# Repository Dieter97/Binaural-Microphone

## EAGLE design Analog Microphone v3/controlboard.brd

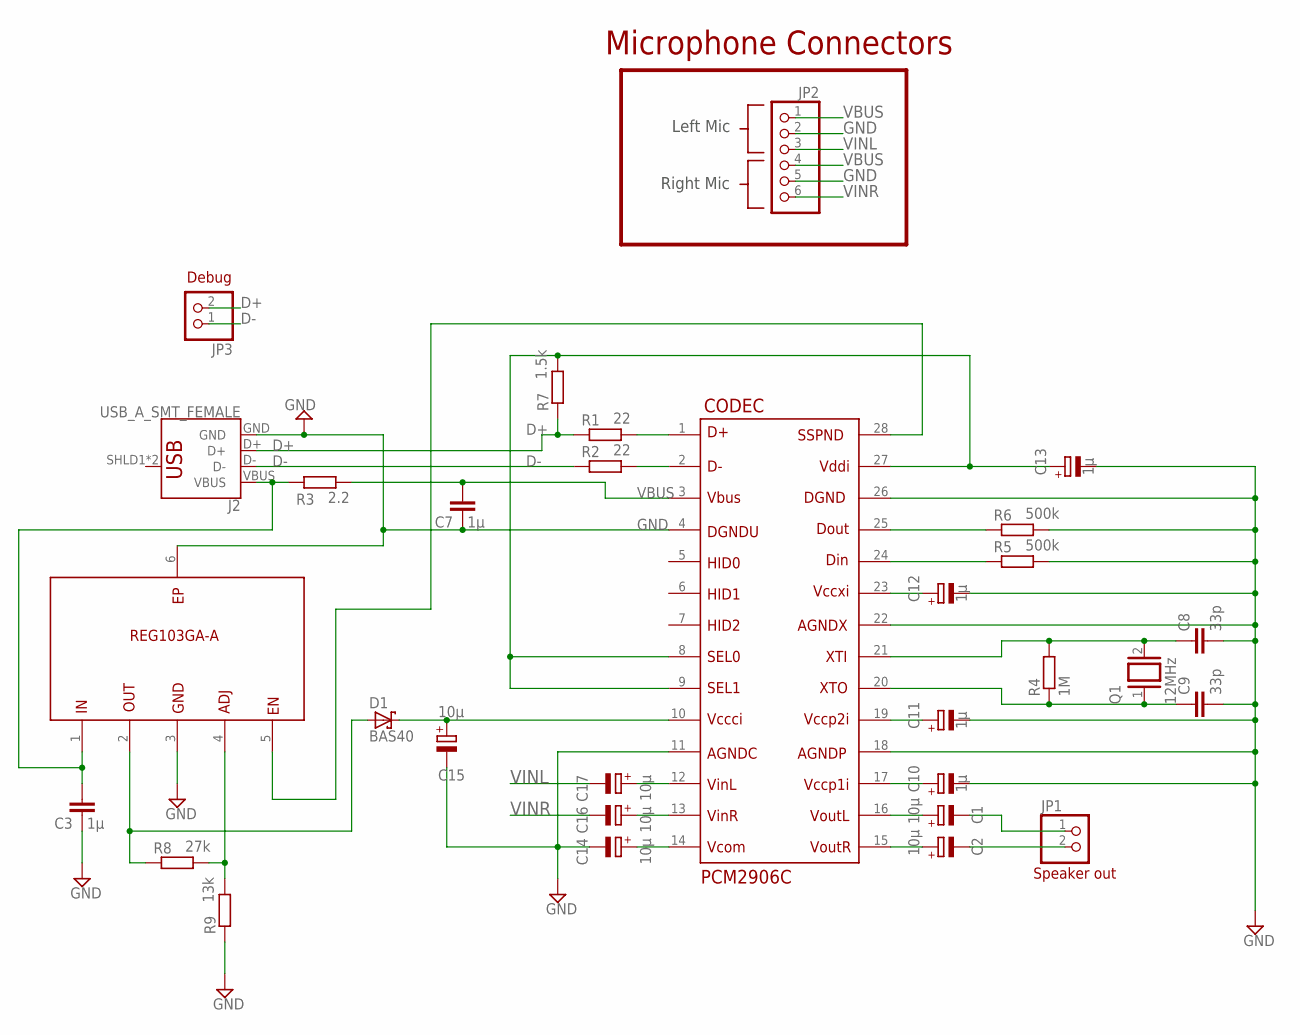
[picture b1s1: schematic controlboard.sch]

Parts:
C1, C2, C14, C15, C16, C17: 10µ; 153CLV-0807
C3, C7: 1µ; C0805
C8, C9: 33p; C0805
C10, C11, C12, C13: 1µ; 153CLV-0807
CODEC: PCM2906C; SOP65P780X200-28N
D1: BAS40; SOT23
J2: USB_A_SMT_FEMALE; USB-A-S-SILK-FEMALE
JP1, JP3: PINHD-1X2; 1X02
JP2: PINHD-1X6; 1X06
Q1: 12MHz; QS
R1, R2: 22; R0805
R3: 2.2; R0805
R4: 1M; R0805
R5, R6: 500k; R0805
R7: 1.5k; R0805
R8: 27k; R0805
R9: 13k; R0805
U$1: REG103GA-A; SOT127P706X180-6N

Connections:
D+: J2.D+, JP3.2, R1.1, R7.1
D-: J2.D-, JP3.1, R2.1
GND: C3.1, C7.1, C8.2, C9.2, C10.-, C11.-, C12.-, C13.-, C14.-, C15.-, CODEC.4, CODEC.11, CODEC.18, CODEC.22, CODEC.26, J2.GND, JP2.2, JP2.5, R5.2, R6.2, R9.1, U$1.3, U$1.6
unnamed: CODEC.1, R1.2
unnamed: CODEC.2, R2.2
unnamed: C11.+, CODEC.19
unnamed: C9.1, CODEC.20, Q1.1, R4.1
unnamed: C8.1, CODEC.21, Q1.2, R4.2
unnamed: C10.+, CODEC.17
unnamed: C12.+, CODEC.23
unnamed: CODEC.25, R6.1
unnamed: CODEC.24, R5.1
unnamed: C13.+, CODEC.8, CODEC.9, CODEC.27, R7.2
unnamed: C15.+, CODEC.10, D1.3 (C)
unnamed: C14.+, CODEC.14
unnamed: CODEC.28, U$1.5
unnamed: C1.+, CODEC.16
unnamed: C2.+, CODEC.15
unnamed: C17.+, CODEC.12
unnamed: C16.+, CODEC.13
unnamed: C1.-, JP1.1
unnamed: C2.-, JP1.2
unnamed: R8.2, R9.2, U$1.4
unnamed: D1.1 (A), R8.1, U$1.2
unnamed: C3.2, J2.VBUS, R3.1, U$1.1
VBUS: C7.2, CODEC.3, JP2.1, JP2.4, R3.2
VINL: C17.-, JP2.3
VINR: C16.-, JP2.6

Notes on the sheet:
Left Mic
Right Mic
Microphone Connectors
Speaker out
Debug

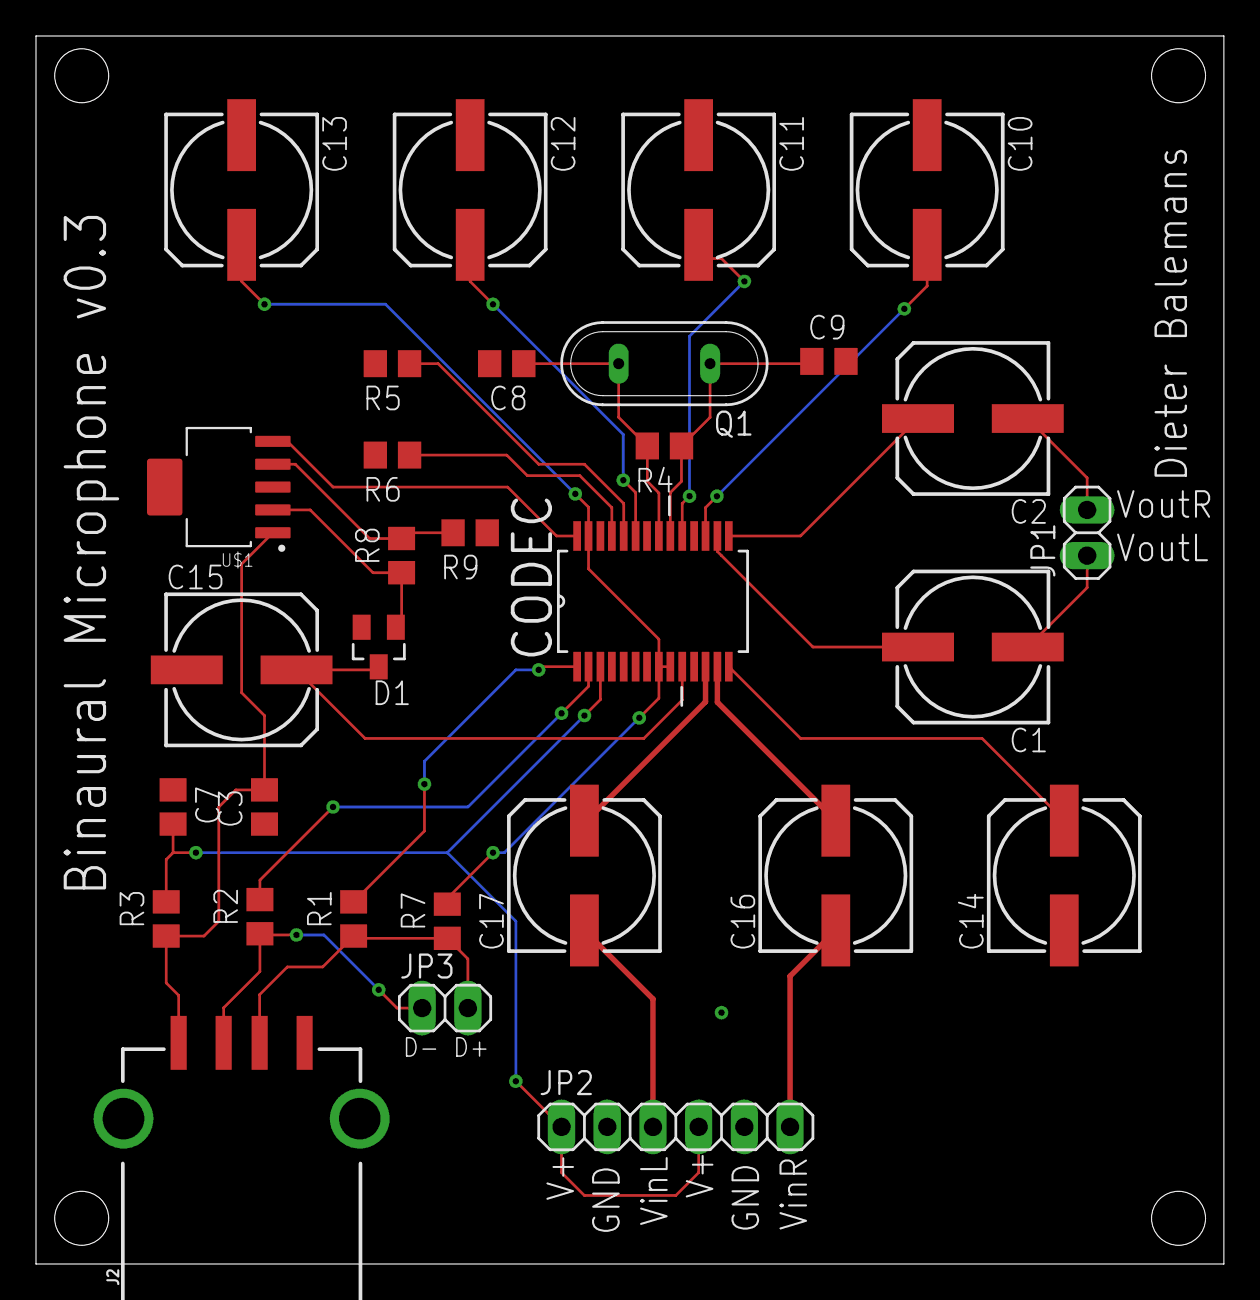
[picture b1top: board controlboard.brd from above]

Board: 2 copper layers, 66.0 x 68.2 mm, 31 parts (0 on the bottom side), 28 nets.

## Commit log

2018-11-06 Cleanup + added version 2 analog microphone + added libraries folder
2018-11-06 Added 3th version of analog board
2018-11-06 Merged lib
2018-11-13 Added bottom ground plane + usb test headers

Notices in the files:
parts and their libraries:
SparkFun-Connectors: Licensing: Creative Commons ShareAlike 4.0 International - https://creativecommons.org/licenses/by-sa/4.0
